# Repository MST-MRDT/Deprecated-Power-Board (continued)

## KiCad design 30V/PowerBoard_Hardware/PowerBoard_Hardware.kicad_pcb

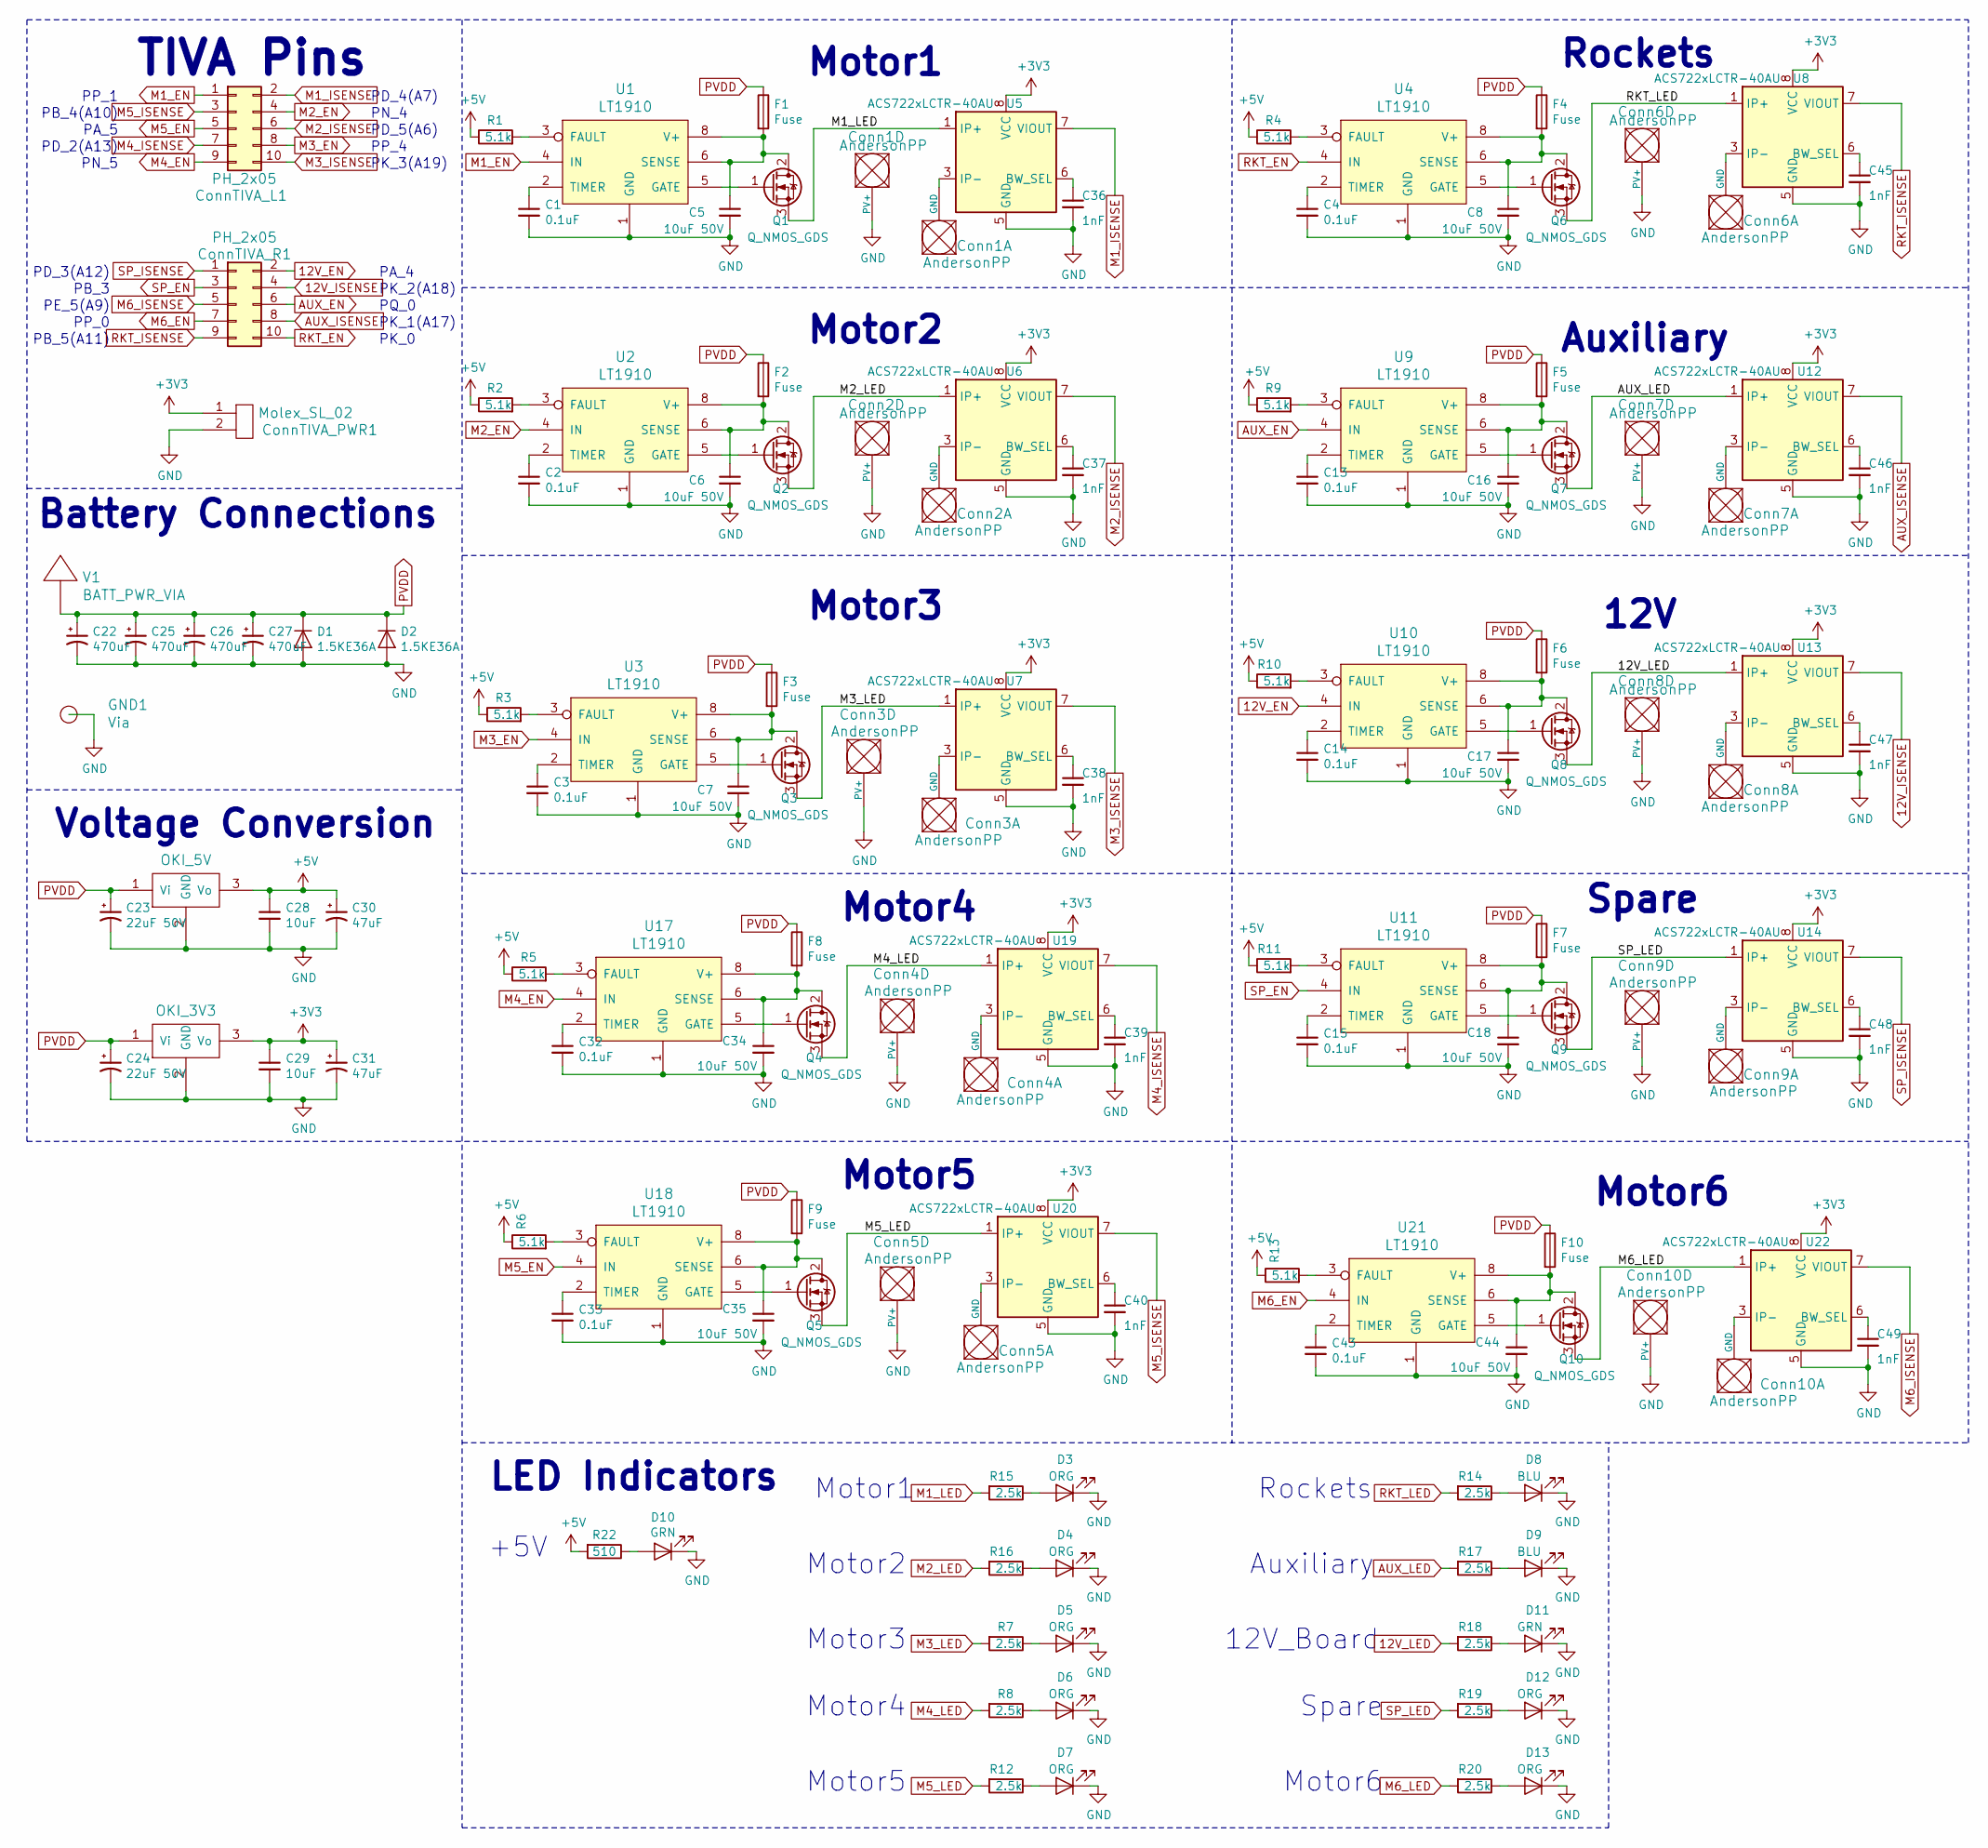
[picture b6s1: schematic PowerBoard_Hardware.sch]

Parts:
C1, C2, C3, C4, C13, C14, C15, C32, C33, C43: 0.1uF; C_0603_1608Metric_Pad1.05x0.95mm_HandSolder
C5, C6, C7, C8, C16, C17, C18, C34, C35, C44: 10uF 50V; C_1206_3216Metric_Pad1.42x1.75mm_HandSolder
C22, C25, C26, C27: 470uF; CP_Radial_D12.5mm_P5.00mm
C23, C24: 22uF 50V; CP_Radial_D6.3mm_P2.50mm
C28, C29: 10uF; C_0603_1608Metric_Pad1.05x0.95mm_HandSolder
C30, C31: 47uF; CP_Radial_D6.3mm_P2.50mm
C36, C37, C38, C39, C40, C45, C46, C47, C48, C49: 1nF; C_0603_1608Metric_Pad1.05x0.95mm_HandSolder
Conn1, Conn2, Conn3, Conn4, Conn5, Conn6, Conn7, Conn8, Conn9, Conn10: AndersonPP; Anderson_2_Horizontal_Stacked
ConnTIVA_L1: PH_2x05; JTAG_ARM_Connector_10_Pin
ConnTIVA_PWR1: Molex_SL_02; MOLEX_SL_02_Vertical
ConnTIVA_R1: PH_2x05; JTAG_ARM_Connector_10_Pin
D1, D2: 1.5KE36A; D_DO-201AD_P5.08mm_Vertical_KathodeUp
D3, D4, D5, D6, D7, D12, D13: ORG; LED_0603_1608Metric_Pad1.05x0.95mm_HandSolder
D8, D9: BLU; LED_0603_1608Metric_Pad1.05x0.95mm_HandSolder
D10, D11: GRN; LED_0603_1608Metric_Pad1.05x0.95mm_HandSolder
F1, F2, F3, F4, F5, F6, F7, F8, F9, F10: Fuse; ATC_Fuse_Block
GND1: Via; BATT_PWR_VIA
Q1, Q2, Q3, Q4, Q5, Q6, Q7, Q8, Q9, Q10: Q_NMOS_GDS; TO-263-2
R1, R2, R3, R4, R5, R6, R9, R10, R11, R13: 5.1k; R_0603_1608Metric_Pad1.05x0.95mm_HandSolder
R7, R8, R12, R14, R15, R16, R17, R18, R19, R20: 2.5k; R_0603_1608Metric_Pad1.05x0.95mm_HandSolder
R22: 510; R_0603_1608Metric_Pad1.05x0.95mm_HandSolder
U1, U2, U3, U4, U9, U10, U11, U17, U18, U21: LT1910; SOIC-8-N7_3.9x4.9mm_P1.27mm
U5, U6, U7, U8, U12, U13, U14, U19, U20, U22: ACS722xLCTR-40AU; SOIC-8_3.9x4.9mm_P1.27mm
U15: OKI_5V; OKI_Horizontal
U16: OKI_3V3; OKI_Horizontal
V1: BATT_PWR_VIA

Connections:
12V_EN: ConnTIVA_R1.2, U10.4 (IN)
12V_ISENSE: ConnTIVA_R1.4, U13.7 (VIOUT)
12V_LED: Q8.3 (S), R18.2, U13.1 (IP+), U13.2 (IP+)
+3V3: C29.1, C31.1, ConnTIVA_PWR1.1, U5.8 (VCC), U6.8 (VCC), U7.8 (VCC), U8.8 (VCC), U12.8 (VCC), U13.8 (VCC), U14.8 (VCC), U16.3 (Vo), U19.8 (VCC), U20.8 (VCC), U22.8 (VCC)
+5V: C28.1, C30.1, R1.1, R2.1, R3.1, R4.1, R5.1, R6.1, R9.1, R10.1, R11.1, R13.1, R22.2, U15.3 (Vo)
AUX_EN: ConnTIVA_R1.6, U9.4 (IN)
AUX_ISENSE: ConnTIVA_R1.8, U12.7 (VIOUT)
AUX_LED: Q7.3 (S), R17.2, U12.1 (IP+), U12.2 (IP+)
GND: C1.2, C2.2, C3.2, C4.2, C5.2, C6.2, C7.2, C8.2, C13.2, C14.2, C15.2, C16.2, C17.2, C18.2, C22.2, C23.2, C24.2, C25.2, C26.2, C27.2, C28.2, C29.2, C30.2, C31.2, C32.2, C33.2, C34.2, C35.2, C36.2, C37.2, C38.2, C39.2, C40.2, C43.2, C44.2, C45.2, C46.2, C47.2, C48.2, C49.2, Conn1.4 (PV+), Conn2.4 (PV+), Conn3.4 (PV+), Conn4.4 (PV+), Conn5.4 (PV+), Conn6.4 (PV+), Conn7.4 (PV+), Conn8.4 (PV+), Conn9.4 (PV+), Conn10.4 (PV+), ConnTIVA_PWR1.2, D1.2 (A), D2.2 (A), D3.1 (K), D4.1 (K), D5.1 (K), D6.1 (K), D7.1 (K), D8.1 (K), D9.1 (K), D10.1 (K), D11.1 (K), D12.1 (K), D13.1 (K), GND1.1, U1.1 (GND), U2.1 (GND), U3.1 (GND), U4.1 (GND), U5.5 (GND), U6.5 (GND), U7.5 (GND), U8.5 (GND), U9.1 (GND), U10.1 (GND), U11.1 (GND), U12.5 (GND), U13.5 (GND), U14.5 (GND), U15.2 (GND), U16.2 (GND), U17.1 (GND), U18.1 (GND), U19.5 (GND), U20.5 (GND), U21.1 (GND), U22.5 (GND)
M1_EN: ConnTIVA_L1.1, U1.4 (IN)
M1_ISENSE: ConnTIVA_L1.2, U5.7 (VIOUT)
M1_LED: Q1.3 (S), R15.2, U5.1 (IP+), U5.2 (IP+)
M2_EN: ConnTIVA_L1.4, U2.4 (IN)
M2_ISENSE: ConnTIVA_L1.6, U6.7 (VIOUT)
M2_LED: Q2.3 (S), R16.2, U6.1 (IP+), U6.2 (IP+)
M3_EN: ConnTIVA_L1.8, U3.4 (IN)
M3_ISENSE: ConnTIVA_L1.10, U7.7 (VIOUT)
M3_LED: Q3.3 (S), R7.2, U7.1 (IP+), U7.2 (IP+)
M4_EN: ConnTIVA_L1.9, U17.4 (IN)
M4_ISENSE: ConnTIVA_L1.7, U19.7 (VIOUT)
M4_LED: Q4.3 (S), R8.2, U19.1 (IP+), U19.2 (IP+)
M5_EN: ConnTIVA_L1.5, U18.4 (IN)
M5_ISENSE: ConnTIVA_L1.3, U20.7 (VIOUT)
M5_LED: Q5.3 (S), R12.2, U20.1 (IP+), U20.2 (IP+)
M6_EN: ConnTIVA_R1.7, U21.4 (IN)
M6_ISENSE: ConnTIVA_R1.5, U22.7 (VIOUT)
M6_LED: Q10.3 (S), R20.2, U22.1 (IP+), U22.2 (IP+)
unnamed: C1.1, U1.2 (TIMER)
unnamed: C2.1, U2.2 (TIMER)
unnamed: C3.1, U3.2 (TIMER)
unnamed: C4.1, U4.2 (TIMER)
unnamed: C5.1, F1.2, Q1.2 (D), U1.6 (SENSE), U1.8 (V+)
unnamed: C6.1, F2.2, Q2.2 (D), U2.6 (SENSE), U2.8 (V+)
unnamed: C7.1, F3.2, Q3.2 (D), U3.6 (SENSE), U3.8 (V+)
unnamed: C8.1, F4.2, Q6.2 (D), U4.6 (SENSE), U4.8 (V+)
unnamed: C13.1, U9.2 (TIMER)
unnamed: C14.1, U10.2 (TIMER)
unnamed: C15.1, U11.2 (TIMER)
unnamed: C16.1, F5.2, Q7.2 (D), U9.6 (SENSE), U9.8 (V+)
unnamed: C17.1, F6.2, Q8.2 (D), U10.6 (SENSE), U10.8 (V+)
unnamed: C18.1, F7.2, Q9.2 (D), U11.6 (SENSE), U11.8 (V+)
unnamed: C32.1, U17.2 (TIMER)
unnamed: C33.1, U18.2 (TIMER)
unnamed: C34.1, F8.2, Q4.2 (D), U17.6 (SENSE), U17.8 (V+)
unnamed: C35.1, F9.2, Q5.2 (D), U18.6 (SENSE), U18.8 (V+)
unnamed: C36.1, U5.6 (BW_SEL)
unnamed: C37.1, U6.6 (BW_SEL)
unnamed: C38.1, U7.6 (BW_SEL)
unnamed: C39.1, U19.6 (BW_SEL)
unnamed: C40.1, U20.6 (BW_SEL)
unnamed: C43.1, U21.2 (TIMER)
unnamed: C44.1, F10.2, Q10.2 (D), U21.6 (SENSE), U21.8 (V+)
unnamed: C45.1, U8.6 (BW_SEL)
unnamed: C46.1, U12.6 (BW_SEL)
unnamed: C47.1, U13.6 (BW_SEL)
unnamed: C48.1, U14.6 (BW_SEL)
unnamed: C49.1, U22.6 (BW_SEL)
unnamed: Conn1.1 (GND), U5.3 (IP-), U5.4 (IP-)
unnamed: Conn2.1 (GND), U6.3 (IP-), U6.4 (IP-)
unnamed: Conn3.1 (GND), U7.3 (IP-), U7.4 (IP-)
unnamed: Conn4.1 (GND), U19.3 (IP-), U19.4 (IP-)
unnamed: Conn5.1 (GND), U20.3 (IP-), U20.4 (IP-)
unnamed: Conn6.1 (GND), U8.3 (IP-), U8.4 (IP-)
unnamed: Conn7.1 (GND), U12.3 (IP-), U12.4 (IP-)
unnamed: Conn8.1 (GND), U13.3 (IP-), U13.4 (IP-)
unnamed: Conn9.1 (GND), U14.3 (IP-), U14.4 (IP-)
unnamed: Conn10.1 (GND), U22.3 (IP-), U22.4 (IP-)
unnamed: D3.2 (A), R15.1
unnamed: D4.2 (A), R16.1
unnamed: D5.2 (A), R7.1
unnamed: D6.2 (A), R8.1
unnamed: D7.2 (A), R12.1
unnamed: D8.2 (A), R14.1
unnamed: D9.2 (A), R17.1
unnamed: D10.2 (A), R22.1
unnamed: D11.2 (A), R18.1
unnamed: D12.2 (A), R19.1
unnamed: D13.2 (A), R20.1
unnamed: Q1.1 (G), U1.5 (GATE)
unnamed: Q2.1 (G), U2.5 (GATE)
unnamed: Q3.1 (G), U3.5 (GATE)
unnamed: Q4.1 (G), U17.5 (GATE)
unnamed: Q5.1 (G), U18.5 (GATE)
unnamed: Q6.1 (G), U4.5 (GATE)
unnamed: Q7.1 (G), U9.5 (GATE)
unnamed: Q8.1 (G), U10.5 (GATE)
unnamed: Q9.1 (G), U11.5 (GATE)
unnamed: Q10.1 (G), U21.5 (GATE)
unnamed: R1.2, U1.3 (FAULT)
unnamed: R2.2, U2.3 (FAULT)
unnamed: R3.2, U3.3 (FAULT)
unnamed: R4.2, U4.3 (FAULT)
unnamed: R5.2, U17.3 (FAULT)
unnamed: R6.2, U18.3 (FAULT)
unnamed: R9.2, U9.3 (FAULT)
unnamed: R10.2, U10.3 (FAULT)
unnamed: R11.2, U11.3 (FAULT)
unnamed: R13.2, U21.3 (FAULT)
PVDD: C22.1, C23.1, C24.1, C25.1, C26.1, C27.1, D1.1 (K), D2.1 (K), F1.1, F2.1, F3.1, F4.1, F5.1, F6.1, F7.1, F8.1, F9.1, F10.1, U15.1 (Vi), U16.1 (Vi), V1.1
RKT_EN: ConnTIVA_R1.10, U4.4 (IN)
RKT_ISENSE: ConnTIVA_R1.9, U8.7 (VIOUT)
RKT_LED: Q6.3 (S), R14.2, U8.1 (IP+), U8.2 (IP+)
SP_EN: ConnTIVA_R1.3, U11.4 (IN)
SP_ISENSE: ConnTIVA_R1.1, U14.7 (VIOUT)
SP_LED: Q9.3 (S), R19.2, U14.1 (IP+), U14.2 (IP+)

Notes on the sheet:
TIVA Pins
12V
Spare
Motor1
Motor2
Motor3
PB_4(A10)
PK_1(A17)
PD_2(A13)
PA_5
LED Indicators
Battery Connections
Voltage Conversion
Auxiliary
Rockets
Motor4
Motor5
Motor6
+5V
12V_Board
PD_3(A12)
PB_3
PQ_0
PN_5
PP_0
PP_1
PE_5(A9)
PK_2(A18)
PD_4(A7)
PB_5(A11)
PK_0
PA_4
PD_5(A6)
PP_4
PN_4
PK_3(A19)

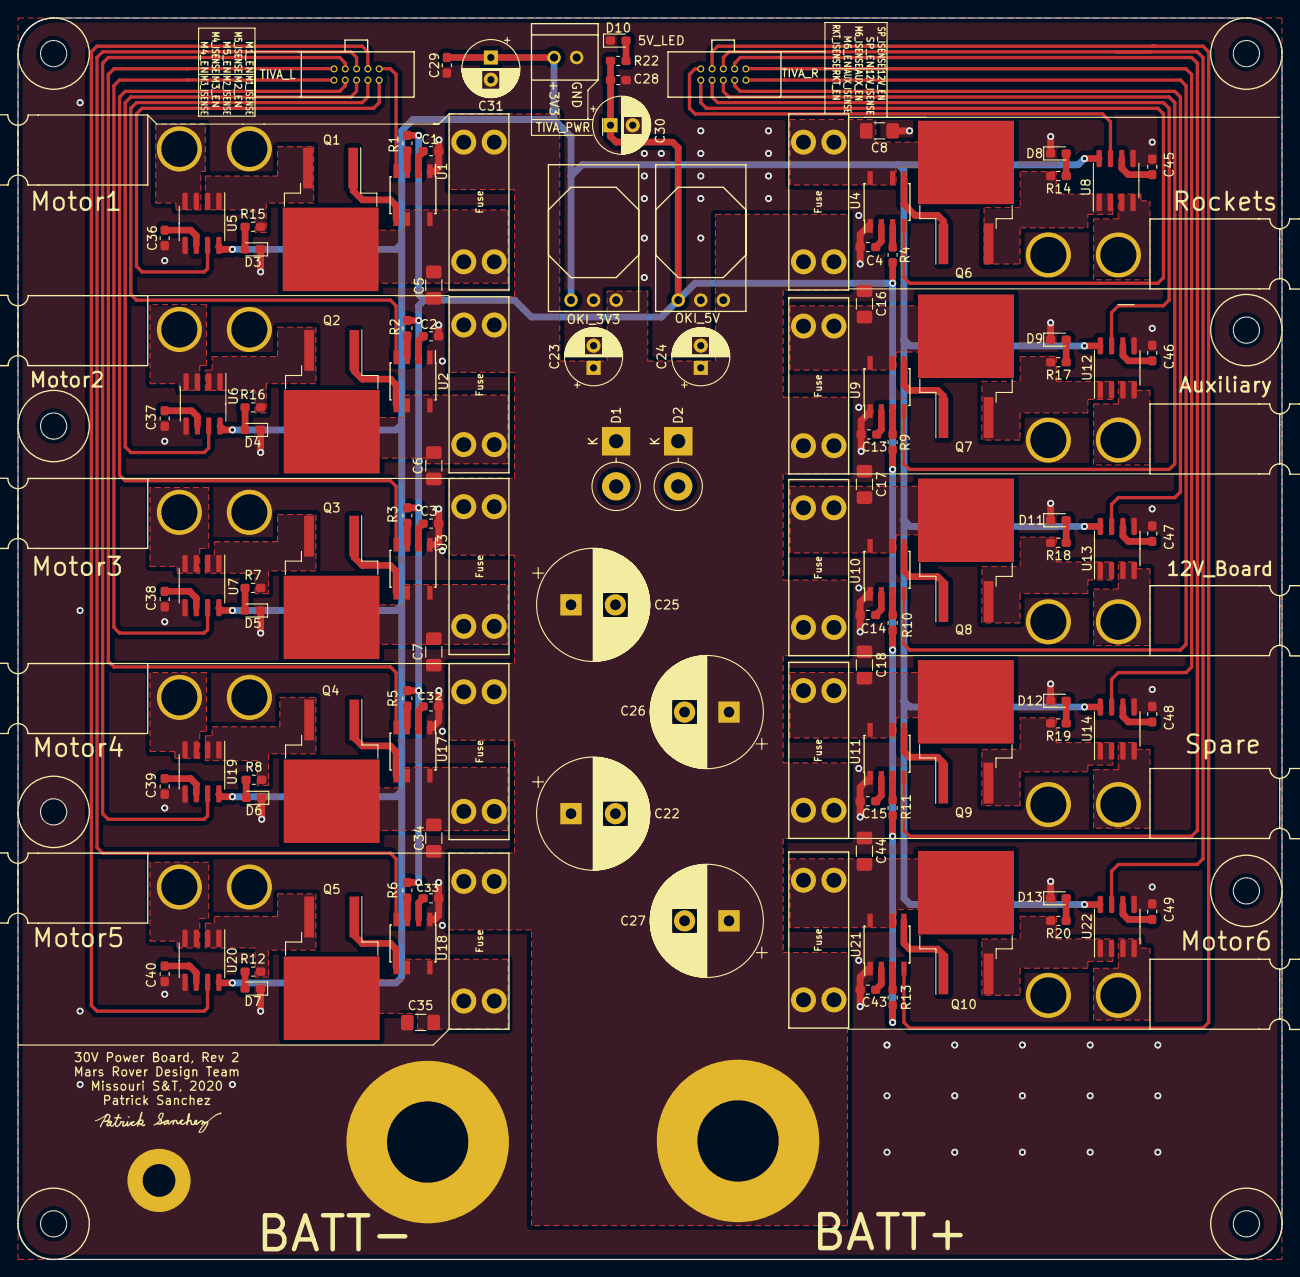
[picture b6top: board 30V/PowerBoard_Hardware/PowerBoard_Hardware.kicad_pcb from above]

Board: 2 copper layers, 142.2 x 139.7 mm, 131 parts (0 on the bottom side), 105 nets.

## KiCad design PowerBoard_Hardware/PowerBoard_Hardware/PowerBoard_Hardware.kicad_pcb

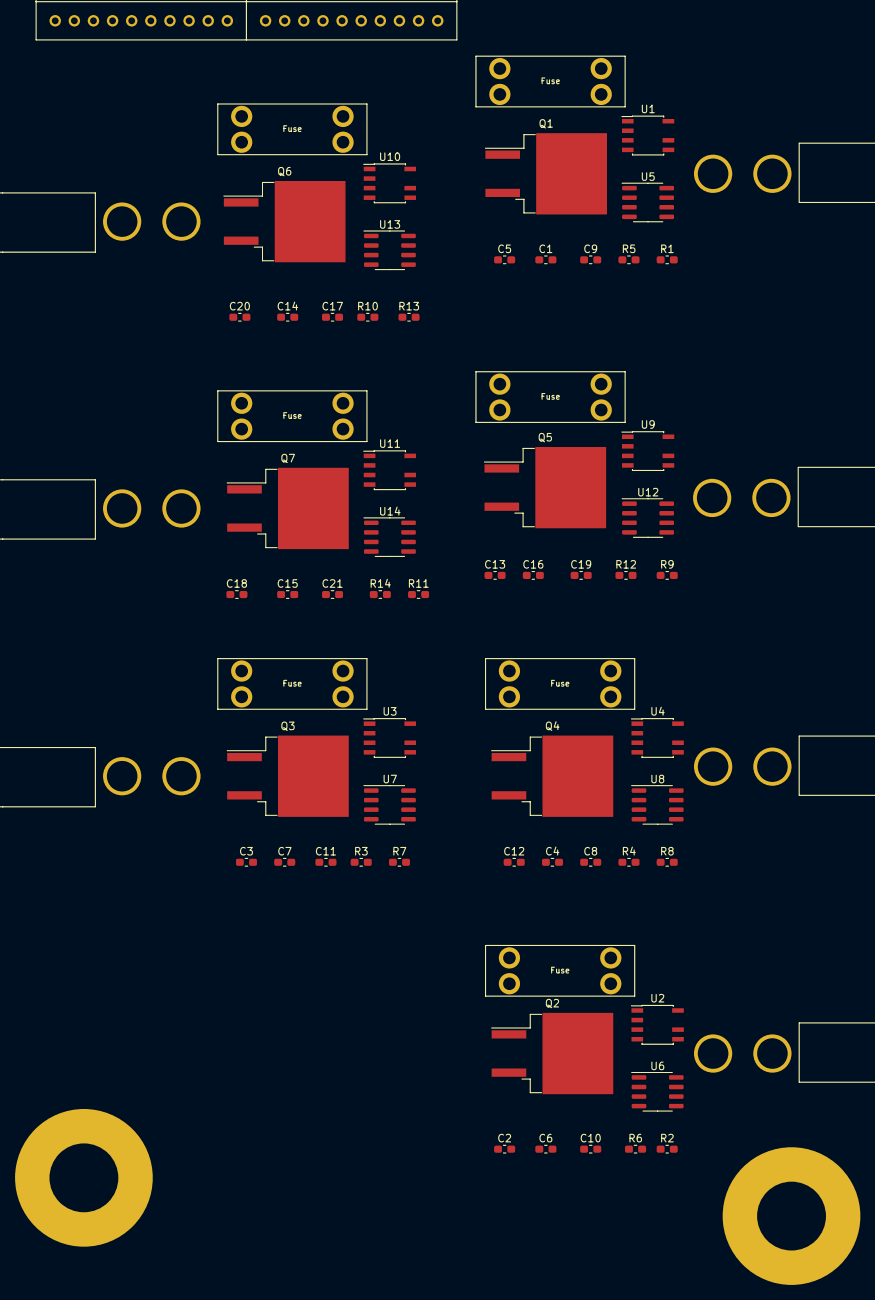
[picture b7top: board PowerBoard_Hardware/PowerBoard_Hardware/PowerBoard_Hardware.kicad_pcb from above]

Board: 2 copper layers, 74 parts (0 on the bottom side), 66 nets, no tracks yet.

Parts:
C1, C2, C3, C4, C9, C10, C11, C12, C13, C14, C15, C19, C20, C21: 0.1 uF; C_0603_1608Metric_Pad1.05x0.95mm_HandSolder
C5, C6, C7, C8, C16, C17, C18: 10 uf; C_0603_1608Metric_Pad1.05x0.95mm_HandSolder
Conn1, Conn15: AndersonPP; BATT_PWR_VIA
Conn2, Conn3: Molex_SL_10; MOLEX_SL_10_Vertical
Conn4, Conn5, Conn6, Conn7, Conn8, Conn9, Conn10: AndersonPP; Anderson_2_Horizontal_Stacked
F1, F2, F3, F4, F5, F6, F7: Fuse; ATC_Fuse_Block
Q1, Q2, Q3, Q4, Q5, Q6, Q7: Q_NMOS_DGS; TO-263-2
R1, R2, R3, R4, R9, R10, R11: 5.1k; R_0603_1608Metric_Pad1.05x0.95mm_HandSolder
R5, R6, R7, R8, R12, R13, R14: 0.01; R_0603_1608Metric_Pad1.05x0.95mm_HandSolder
U1, U2, U3, U4, U9, U10, U11: LT1910; SOIC-8-N7_3.9x4.9mm_P1.27mm
U5, U6, U7, U8, U12, U13, U14: ACS722xLCTR-40AU; SOIC-8_3.9x4.9mm_P1.27mm

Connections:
+5V: Conn3.1, R1.1, R2.1, R3.1, R4.1, R9.1, R10.1, R11.1
GND: C1.2, C2.2, C3.2, C4.2, C5.2, C6.2, C7.2, C8.2, C9.2, C10.2, C11.2, C12.2, C13.2, C14.2, C15.2, C16.2, C17.2, C18.2, C19.2, C20.2, C21.2, Conn1.1, Conn3.2, Conn4.1, Conn5.1, Conn6.1, Conn7.1, Conn8.1, Conn9.1, Conn10.1, U1.1, U2.1, U3.1, U4.1, U5.5, U5.6, U6.5, U6.6, U7.5, U7.6, U8.5, U8.6, U9.1, U10.1, U11.1, U12.5, U12.6, U13.5, U13.6, U14.5, U14.6
unnamed: C1.1, U1.2
unnamed: C2.1, U2.2
unnamed: C3.1, U3.2
unnamed: C4.1, U4.2
unnamed: C9.1, U5.8
unnamed: C10.1, U6.8
unnamed: C11.1, U7.8
unnamed: C12.1, U8.8
unnamed: C13.1, U9.2
unnamed: C14.1, U10.2
unnamed: C15.1, U11.2
unnamed: C19.1, U12.8
unnamed: C20.1, U13.8
unnamed: C21.1, U14.8
unnamed: F1.1, U5.3, U5.4
unnamed: F2.1, U6.3, U6.4
unnamed: F3.1, U7.3, U7.4
unnamed: F4.1, U8.3, U8.4
unnamed: F5.1, U12.3, U12.4
unnamed: F6.1, U13.3, U13.4
unnamed: F7.1, U14.3, U14.4
unnamed: Q1.1, R5.2, U1.6
unnamed: Q1.2, U1.5
unnamed: Q1.3, U5.1, U5.2
unnamed: Q2.1, R6.2, U2.6
unnamed: Q2.2, U2.5
unnamed: Q2.3, U6.1, U6.2
unnamed: Q3.1, R7.2, U3.6
unnamed: Q3.2, U3.5
unnamed: Q3.3, U7.1, U7.2
unnamed: Q4.1, R8.2, U4.6
unnamed: Q4.2, U4.5
unnamed: Q4.3, U8.1, U8.2
unnamed: Q5.1, R12.2, U9.6
unnamed: Q5.2, U9.5
unnamed: Q5.3, U12.1, U12.2
unnamed: Q6.1, R13.2, U10.6
unnamed: Q6.2, U10.5
unnamed: Q6.3, U13.1, U13.2
unnamed: Q7.1, R14.2, U11.6
unnamed: Q7.2, U11.5
unnamed: Q7.3, U14.1, U14.2
unnamed: R1.2, U1.3
unnamed: R2.2, U2.3
unnamed: R3.2, U3.3
unnamed: R4.2, U4.3
unnamed: R9.2, U9.3
unnamed: R10.2, U10.3
unnamed: R11.2, U11.3
PA_6: Conn3.8, U6.7
PB_2: Conn2.9, U14.7
PB_3: Conn2.10, U8.7
PC_4: Conn2.3, U11.4
PC_5: Conn2.4, U4.4
PD_3: Conn2.7, U5.7
PD_7: Conn3.7, U12.7
PE_0: Conn3.3, U1.4
PE_1: Conn3.4, U9.4
PE_2: Conn3.5, U2.4
PE_3: Conn3.6, U10.4
PE_4: Conn2.2, U3.4
PM_4: Conn3.9, U13.7
PM_5: Conn3.10, U7.7
PVDD: C5.1, C6.1, C7.1, C8.1, C16.1, C17.1, C18.1, R5.1, R6.1, R7.1, R8.1, R12.1, R13.1, R14.1, U1.8, U2.8, U3.8, U4.8, U9.8, U10.8, U11.8

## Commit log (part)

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2016-01-17 New Layout Idea
2016-01-17 Routed new layout
2016-01-18 Jake started routing 4 layer board
2016-01-18 Changed 5V Caps
2016-01-18 rerouting...
2016-01-19 Finished routing 4-layer
2016-01-21 github sucks
2016-01-21 FINAL REV2 - ORDERED SIERRA CIRCUITS
    didnt actually change anything
2016-02-11 osh stencil gerbers
2016-03-13 Moved around 12v bucks, routed ORing mosfet circuits
2016-03-13 Changed ORing FETs to DPAK
2016-04-05 Routed, moved some motor fets over
2016-04-10 Changed 5V on/off circuit, enlarged planes
2016-04-11 Final Power Board 2016 Rev 2
    generated gerbers
2016-04-16 Swapped LM74670 with LM5050
2016-04-17 Generated gerbers
2016-04-20 Improved some top planes
2017-10-04 Added 2014 branch so I can release the 2014 files
2017-10-04 added 2015 specific branch so I can draft a release
2019-10-02 Pass 1.2
    *Circuit has been consolidated
    *All 6 circuits have been added
2019-10-04 Pass 1.4
    *Fuses have been added after each anderson
2019-10-09 Pass 1.5
    *pvv changed to PVDD
    *Fuses placed before each anderson
    *pcb layout generated
    *PVDD via has issues
2019-11-12 Pass 1.7
2019-12-13 Overwriting for proper file structure
2019-12-14 Ready for PRR
2019-12-14 made schematic prettier
2019-12-14 fixed schematic b/c Zac made fun of me
2019-12-19 Regenerated gerbs (No drill files Iguess)
2020-01-21 Created step file
2020-02-07 All 3V3 connected, need to fix silkscreen and move connectors
2020-02-15 Ready for Rev 2 review, minus frame ground
2020-02-17 updated gerbs
2020-09-14 Added Folders
2020-09-30 Tiva Schematic
2020-10-02 Started Current and LT1910 circuits
    Mosfet and current sensor for one port made
2020-10-05 Busses
    Continued wiring driver, busses, and current sensors on sheet 2
2020-10-05 Rearranging
    slight changes to wire placement, no major changes
2020-10-13 added hierarchical labels, changed current sensor, added 12V labels to TIVA, finished buck sheet
2020-10-14 Extra Bus, Connectors moved to top level
    Added "Extra" 20A bus, tiva pins, and anderson
    Moved molex connector out of tiva sheet so it is visible on top sheet
    Removed "Power In" sheet to bring vias to top sheet.
2020-10-15 Added 5th Motor
    Added Motor 5 to Motor Busses, added tiva pins and anderson connections
    Renamed Extra 5 to Extra 6
2020-10-15 Matching 12V Tiva Pins
    Renamed 12 tiva pins to match their names on 12V board
    Changed molex connections to match those on 12V board
    Removed LowExtra_CTL as it is not present on 12V connector
2020-10-15 updated busses, fuses, and some names
2020-10-16 Fixed Hierarchial Pins/Labels
    Removed Hierarchal labels from top sheet and replaced them with pins linked to the subsheets.
    Renamed M5 Tiva pin to D1
2020-10-22 Updated molex connector (Still need tiva pin)
2020-10-23 Rearranged Bucks and Fixed 12V Bus LED Resistor
    Moved 5v bus to the middle and 3.3V bus to the bottom to make things more clear.
    12 bus had 3300 ohm resistor when it should have 1200 ohm b/c it only has 12 V going into it
2020-10-26 Added GimbalSense, reannotated
2020-10-29 Added Footprints (Still missing MOSFET)
2020-11-07 Changed capacitor footprints
    Changed 1000uF and 470uF capacitor footprints. Imported footprint for 470uF so it might need looking at.
    Changed unpolarized 1000uF capacitors in bucks to polarized capacitors
2020-11-15 started editing layout
2020-11-16 Layout
2020-11-17 Rearranging Planes
2020-11-17 added auxillary components to layout
2020-11-17 Added Driveboard Bus, Fixed Pads
2020-11-18 rearranged components on layout
2020-11-18 Added Planes to Aux, Vaccum, 12V busses, started swapping shunt resistors and sensors
2020-11-19 added all components to board
2020-11-19 Finished Busses, Fixed Vias in Pads, Connected Okis & Buck
2020-11-22 Rocket and 12V bus connected
2020-11-22 All Busses connected to Tiva, LEDs connected
2020-11-23 labelled LEDs
2020-11-23 3D graphics
2020-11-26 Made room for mounting holes
2020-11-27 Moved vias, changed isolated pad of resistors to no net
2020-11-27 Added signature folder and my signature to board
2020-11-27 Tiva pins
2020-11-27 Moved PV plane from under mounting hole
2020-11-29 started BOM file
2020-12-04 footprint update
    -andersons made vertical
    -current resistor footprint updated
2020-12-07 Buck Layout
2020-12-07 12 Tiva pins rearranged
2020-12-08 Tiva Layout updated
2020-12-10 motors
    changed name of components in layout to match schematic
2020-12-11 Tiva pins connected, okis connected
2020-12-11 Updated Silkscreen
2020-12-14 updated BOM
2020-12-14 Completed Gerbs
2021-01-05 BOM updated
    some components were chosen incorrectly
2021-02-18 changed mosfet footprint so its actually right
2021-03-12 updated mosfet footprints
    but for real this time
2021-03-12 rearranged components (layout)
2021-03-19 circuit, deletes
    made circuit to copy across board (hopefully);
    deleted old traces that "aren't wide enough"
2021-03-20 uhh more circuits
    finished top circuits on layout, fixed two resistors in schematic
2021-03-22 finished circuits
    finished main circuits
2021-03-22 molexes
    - changed 5 pin molex to 4 pin molex (removed buckCTL)
    - started making traces from molexes to tiva
2021-03-23 mounting holes
    got placed
2021-04-10 gerbs made
2021-04-28 Revert "netlist"
    This reverts commit 1af6446f6858f10edba603e339066d14f3a2f95b.
2021-04-28 netlist for power andersons
2021-10-01 Finished bucks & started implementation of the TIVA
2021-10-06 Added sheets for 12V
2021-10-07 Added other pack MOSFETS
2021-10-08 Created global tags in main sheet
2021-10-10 Fixed some stuff
2021-10-21 Minor changes with Powerboard PDF
2021-10-21 Minor changes
2021-11-11 Assigned Footprints to Symbols
2021-11-12 Made it to layout, found out about gnd via
2021-11-12 Started on the layout of the board
    Made the outline of the board, organized anderson connections so they are easily distinguishable, and added ground planes on front and back copper
2021-11-12 Organized parts
2021-11-12 fixed Fuses
2021-11-13 Revert Previous merge
2021-11-13 Layout changes
2021-11-14 Revert "Placed Components for Motor 1 and fixed errors with netlist"
    This reverts commit 86a32237b1b6d07fe668dfe10dac6f9ef44dc23b.
2021-11-14 Fixed a few errors and started wiring motor 1
2021-11-14 Wired connections for a couple of motors
2021-11-15 wires for motor 1
2021-11-16 Added SciAct to the Board
2021-11-16 Rearranged layout to keep actuation next to logic
2021-11-16 Started placing GimAct components
2021-11-17 Changed a lot, made the whole ass front plane pack, and questioned everything
2021-11-17 Organized
2021-11-17 Connected GND pads to GND
2021-11-17 Fixed and wired first four motor circuits
2021-11-17 Connected the TIVA to PVACT1, PVACT2, Pack, and PV2
2021-11-17 Added tag for circuits
2021-11-18 Worked on Cam 1 & 2 and started with Multimedia
2021-11-18 Added more sikscreen stuff
2021-11-21 double all of the anderson names, and fuse ratings.
2021-11-21 PV is not needed in the center of the board, change the PV plane to be a U shape and have the center of that (on the front plane) be gnd instead
2021-11-28 Changed Anderson Plane Sizes to .25'' or higher
2021-11-29 Net plane changes
2021-11-30 Replaced 12v okis w/big buck. Changed .0025 resistors to not 603.
2021-11-30 Fixed tags
2021-12-03 changed MOSFET names to what we're actually using
2021-12-04 Closing kicad + bom stuff
2021-12-05 Changed the footprint for the shunt resistors and loaded the netlist to the layout
2021-12-05 Cleaned up board and set dimensions with new board size
2021-12-05 Finished example for PV circuit and moved TIVA layout
2021-12-05 added screw holes
2021-12-11 Organized PV M1 Circuit
2021-12-11 Added GND and PV planes and organized everything onto the board except for 12V circuits
2021-12-12 Did a lot of shit Pt.1
2021-12-12 Did a lot of shit Pt.2
2021-12-13 Connected the TIVA up
2021-12-17 fixed gimbal anderson (tentative on the field changes)
2021-12-17 Cleared wire connections and set up board for new connections
2021-12-22 Brought all the connections from the components closer to the location of the TIVA
2021-12-22 added ground planes for the two middle layers
2022-02-11 Fixed the labels on the drive anderson and fixed U61 & C106 not being grounded
2022-02-11 Grounded OKI LEDS
2022-02-17 added motors, okis, vias, and teensy
2022-02-18 fixed anderson tags
2022-02-18 added 12V anderson
2022-02-26 Cleaned up main page and added POE Current sense and driver
2022-02-26 Changed Resistor Values Pt.2
2022-03-08 Implementing the tiva into Pack
2022-03-08 Tiva changes, just driver pins now.
2022-03-09 saving
2022-03-10 Back to TEENSY
2022-03-10 Organizing stuff
2022-03-10 assigned Molex footprints
2022-03-12 Somewhat completed schematic
    did stuff
2022-03-13 Wired a few circuits, mainly oki and ethernet and M1
2022-03-13 Added all the components to the board and began wiring them together
2022-03-15 more wiring
2022-03-18 fixed schematic issues - renamed ports, removed unnecessary ports, corrected footprint assignments; began layout - created circuits for most ports, most components placed
2022-03-18 All connections made
2022-04-06 Generated step file
2022-09-24 finished schematic
2022-09-24 Added Fuses
2022-09-26 Made Most of the Review Changes
2022-10-02 Assigned Footprints
2022-10-11 Added Fuses, Potential Layout for Connector 1
2022-10-11 Placed Power Vias, Set Up Oki and Power Filter
2022-10-16 MOSFET Layouts
2022-10-23 Traces and silkscreen
2022-10-28 Layout edits
2022-11-06 Layout Review Changes
2022-11-07 updates ;)
2022-11-11 edits
    added 3d fuse blocks ;P
2022-11-19 generated Gerbs
2023-01-13 added pull down resistors to gates of nfets
2023-01-29 Fixed Resistor Values
2023-02-08 Made Schematic Review Changes
2023-03-03 20A Current Sensing Blocks on Layout
2023-03-15 Further progress on port blocks in layout
2023-03-15 More layout, mostly done except signal traces
2023-03-19 Layout done except ethernet and vias
2023-03-20 High current ports reblocked with 4-layer board
2023-03-20 more layout
2023-03-20 Layout Finished
2023-03-21 generated gerbs and fixed files
2023-04-21 New Schematic, Added 12V and Battery Backup
2023-04-22 Components Arranged on Layout
2023-04-22 Layout Traces Finished
2023-09-08 2024 Rev1
    Created 2024 Rev1 Branch
    Outlined main features on schematic
2023-09-13 troubleshooting push issues
    added an anderson
2023-09-13 test push again
    added another anderson
2023-09-18 Changes
    New Current Sensing Component
    Mosfet Resistor values change
    Still needs plenty of work
2023-09-25 Schematic Changes P1
    Current Sensing Changes
    24V Converter
2023-09-25 Schematic Changes P3
    Current Sensing Stuff
    Other Stuff
2023-09-29 10K 5A V.Div. Revision
    removed 3 3.3K and 3 6.8K and replace with 6 10K resistors
2023-10-03 Finished Adding NetSwitch3 24V Buck
    -Both 24V buck capacitors changed to correct value.
    -Made Net Switch_3 24V buck have its own global variable for 24V output.
    -Moved global label slightly off of teensy pins so a bit of wire is showing.
    -I believe I removed the unnecessary 24V buck trace.
    IMPORTANT NOTICE
    NetSwitch3 Current Sensing variable hasn't been connected to the teensy because the teensy is out of analog spots. Garret said he'll look at it and let us know where to put it.
2023-10-08 Layout Started
    Fixed footprints
    Started Layout
    Lots of work left to be done
2023-10-11 Fill gnd plane
    discussed stuff & goofed
2023-10-15 Layout Stuff Rev1
2023-10-15 Layout Review Ready
    Made the traces pretty
2023-10-20 I changed the C6 to 1206 from 0603
    cap rated 35v, sees PV = needed to change cap = must alter footprint
2023-10-31 Organize components
2023-10-31 Layout Traces
    Finished Trace Work
    Added Signature
2023-11-01 Added Dylan Dush Signature
    I added my signature of 20mm x 7.4mm.
2023-11-01 Silkscreens
2023-11-01 Added my signature
    :)
2023-11-02 Added PV and GND Silkscreen
2023-11-03 Finished Third Review Layout
2023-11-08 User Drawings
2023-11-10 PFET Change
    Changed PFET
    Generated Gerbs
